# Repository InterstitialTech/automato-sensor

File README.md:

# automato-sensor
sensor module for the Automato ecosystem

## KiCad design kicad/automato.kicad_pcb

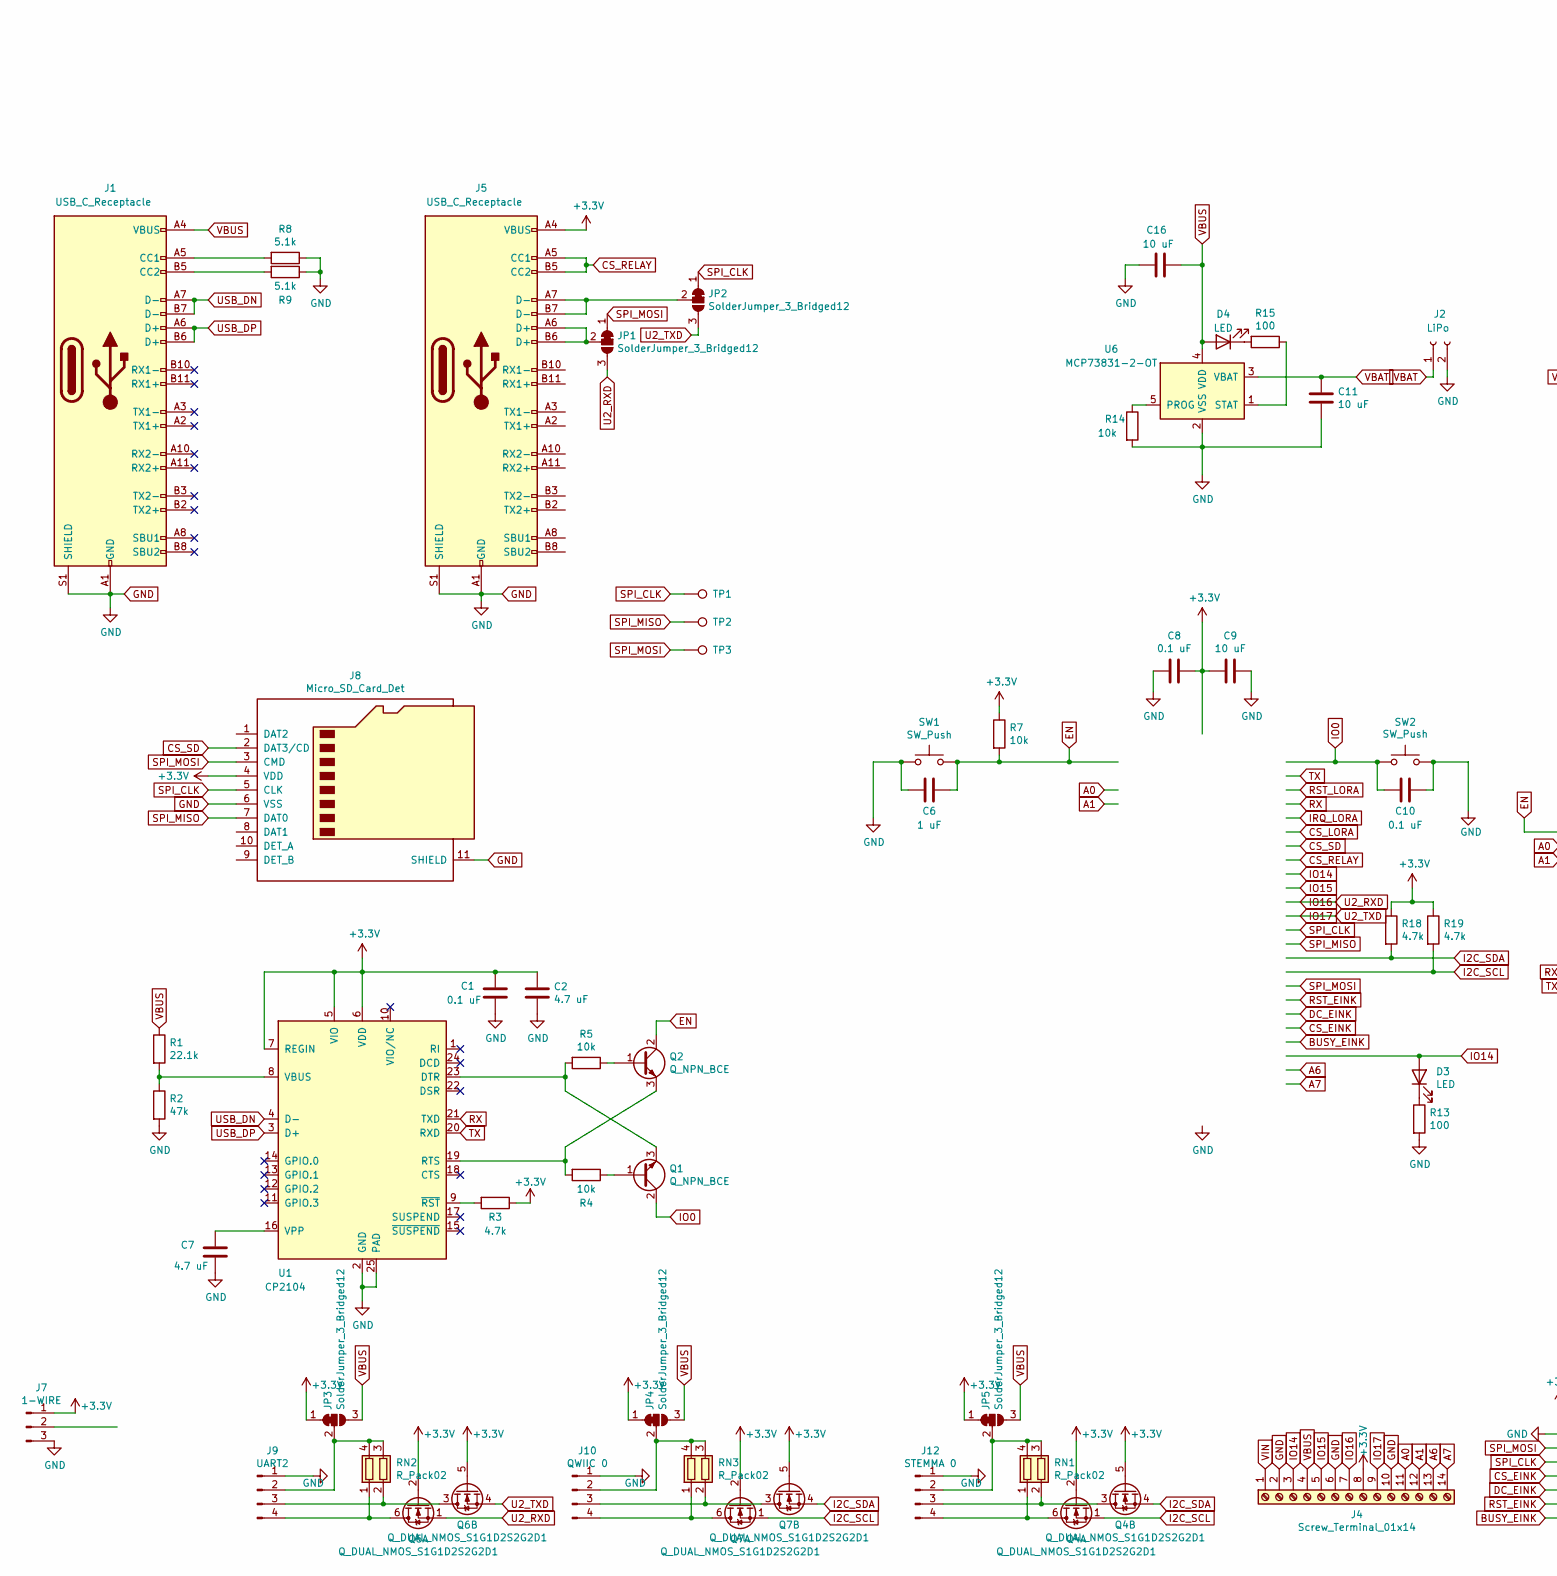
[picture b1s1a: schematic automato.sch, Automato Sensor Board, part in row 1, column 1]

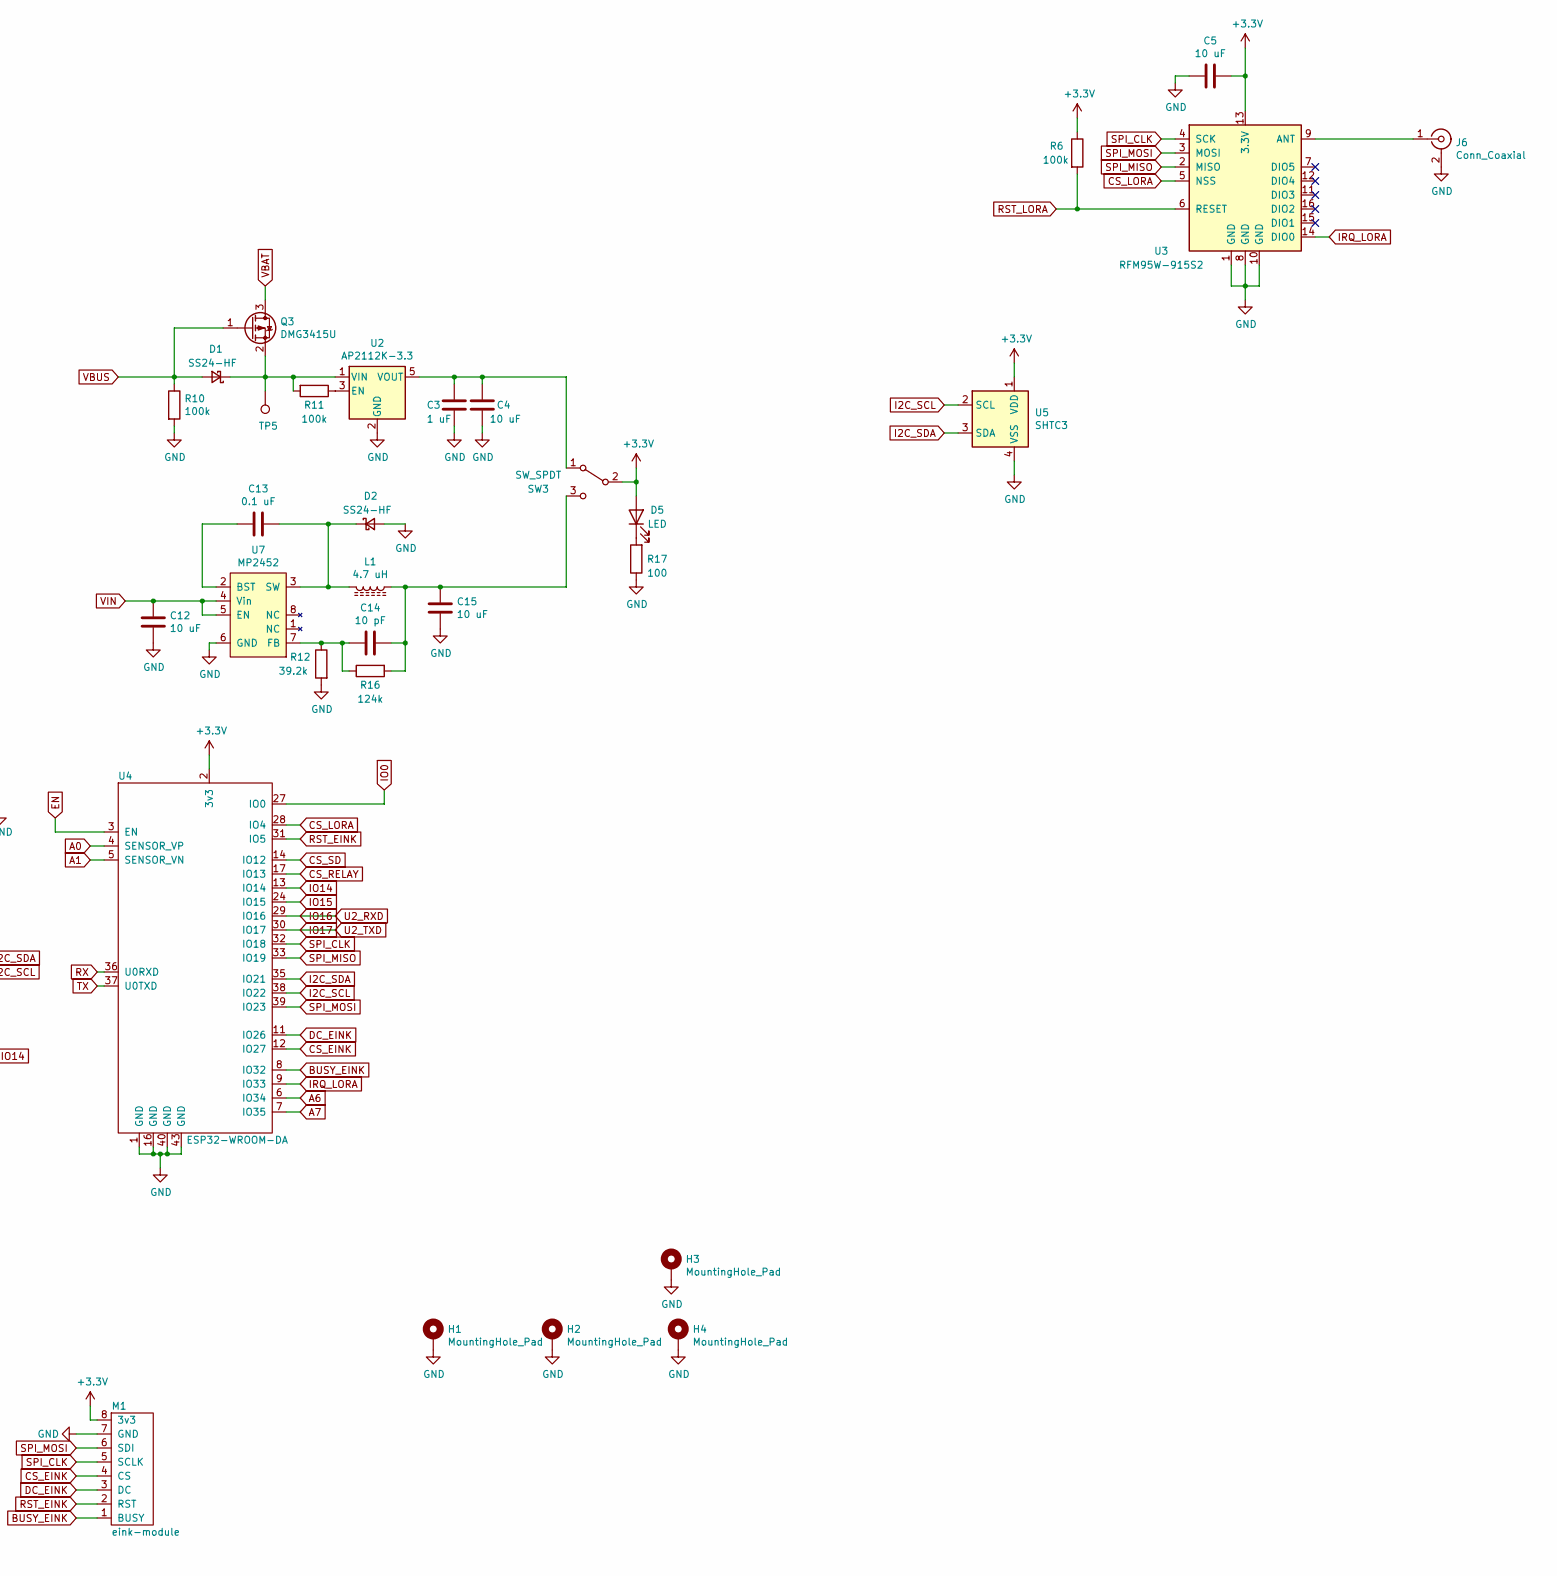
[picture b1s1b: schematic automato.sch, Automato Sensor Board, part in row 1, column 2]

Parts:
C1, C8, C10, C13: 0.1 uF; C_0805_2012Metric
C2, C7: 4.7 uF; C_0805_2012Metric
C3, C6: 1 uF; C_0805_2012Metric
C4, C5, C9, C11, C12, C15, C16: 10 uF; C_0805_2012Metric
C14: 10 pF; C_0805_2012Metric
D1, D2: SS24-HF; D_SMA
D3, D4, D5: LED; LED_0603_1608Metric_Castellated
H1, H2, H3, H4: MountingHole_Pad; MountingHole_3.2mm_M3_Pad_TopBottom
J1, J5: USB_C_Receptacle; USB_C_Receptacle_Amphenol_12401610E4-2A_CircularHoles
J2: LiPo; JST_PH_B2B-PH-K_1x02_P2.00mm_Vertical
J4: Screw_Terminal_01x14; TerminalBlock_Phoenix_PT-1,5-14-3.5-H_1x14_P3.50mm_Horizont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
J6: Conn_Coaxial; SMA_Molex_73251-1153_EdgeMount_Horizontal
J7: 1-WIRE; JST_PH_S3B-PH-SM4-TB_1x03-1MP_P2.00mm_Horizontal
J8: Micro_SD_Card_Det; MEM2051-00-195-00-A
J9: UART2; JST_PH_S4B-PH-SM4-TB_1x04-1MP_P2.00mm_Horizontal
J10: QWIIC 0; JST_SH_SM04B-SRSS-TB_1x04-1MP_P1.00mm_Horizontal
J12: STEMMA 0; JST_PH_S4B-PH-SM4-TB_1x04-1MP_P2.00mm_Horizontal
JP1, JP2, JP3, JP4, JP5: SolderJumper_3_Bridged12; SolderJumper-3_P1.3mm_Bridged12_RoundedPad1.0x1.5mm
L1: 4.7 uH; L_1008_2520Metric
M1: eink-module
Q1, Q2: Q_NPN_BCE; SOT-23
Q3: DMG3415U; SOT-23
Q4, Q6, Q7: Q_DUAL_NMOS_S1G1D2S2G2D1; SOT-23-6
R1: 22.1k; R_0805_2012Metric
R2: 47k; R_0805_2012Metric
R3, R18, R19: 4.7k; R_0805_2012Metric
R4, R5, R7, R14: 10k; R_0805_2012Metric
R6, R10, R11: 100k; R_0805_2012Metric
R8, R9: 5.1k; R_0805_2012Metric
R12: 39.2k; R_0805_2012Metric
R13, R15, R17: 100; R_0805_2012Metric
R16: 124k; R_0805_2012Metric
RN1, RN2, RN3: R_Pack02; R_Array_Concave_2x0603
SW1, SW2: SW_Push; SW_SPST_EVQPE1
SW3: SW_SPDT; L102021ML04Q
TP1, TP2, TP3, TP5: TestPoint; TestPoint_Pad_D2.0mm
U1: CP2104; QFN-24-1EP_4x4mm_P0.5mm_EP2.6x2.6mm
U2: AP2112K-3.3; SOT-23-5
U3: RFM95W-915S2; HOPERF_RFM9XW_SMD
U4: ESP32-WROOM-DA
U5: SHTC3; Sensirion_DFN-4-1EP_2x2mm_P1mm_EP0.7x1.6mm
U6: MCP73831-2-OT; SOT-23-5
U7: MP2452; DFN-8-1EP_3x2mm_P0.5mm_EP1.75x1.45mm

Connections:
+3V3: C1.1, C2.1, C5.1, C8.1, C9.2, D5.2 (A), J4.8, J5.A4 (VBUS), J5.A9 (VBUS), J5.B4 (VBUS), J5.B9 (VBUS), J7.1, J8.4 (VDD), JP3.1 (A), JP4.1 (A), JP5.1 (A), M1.8 (3v3), Q4.2 (G), Q4.5 (G), Q6.2 (G), Q6.5 (G), Q7.2 (G), Q7.5 (G), R3.1, R6.1, R7.1, R18.1, R19.1, SW3.2 (B), U1.5 (VIO), U1.6 (VDD), U1.7 (REGIN), U3.13 (3.3V), U4.2 (3v3), U5.1 (VDD)
A0: J4.11, U4.4 (SENSOR_VP)
A1: J4.12, U4.5 (SENSOR_VN)
A6: J4.13, U4.6 (IO34)
A7: J4.14, U4.7 (IO35)
BUSY_EINK: M1.1 (BUSY), U4.8 (IO32)
CS_EINK: M1.4 (CS), U4.12 (IO27)
CS_LORA: U3.5 (NSS), U4.28 (IO4)
CS_RELAY: J5.A5 (CC1), J5.B5 (CC2), U4.17 (IO13)
CS_SD: J8.2 (DAT3/CD), U4.14 (IO12)
DC_EINK: M1.3 (DC), U4.11 (IO26)
EN: C6.1, Q2.2 (C), R7.2, SW1.2, U4.3 (EN)
GND: C1.2, C2.2, C3.2, C4.2, C5.2, C6.2, C7.2, C8.2, C9.1, C10.1, C11.2, C12.2, C15.2, C16.1, D2.2 (A), H1.1, H2.1, H3.1, H4.1, J1.A1 (GND), J1.A12 (GND), J1.B1 (GND), J1.B12 (GND), J1.S1 (SHIELD), J2.2, J4.2, J4.6, J4.10, J5.A1 (GND), J5.A12 (GND), J5.B1 (GND), J5.B12 (GND), J5.S1 (SHIELD), J6.2 (Ext), J7.3, J8.6 (VSS), J8.11 (SHIELD), J9.1, J10.1, J12.1, M1.7 (GND), R2.2, R8.1, R9.1, R10.2, R12.2, R13.2, R14.2, R17.1, SW1.1, SW2.2, U1.2 (GND), U1.25 (PAD), U2.2 (GND), U3.1 (GND), U3.8 (GND), U3.10 (GND), U4.1 (GND), U4.16 (GND), U4.40 (GND), U4.43 (GND), U5.4 (VSS), U6.2 (VSS), U7.6 (GND)
I2C_SCL: Q4.1 (S), Q7.1 (S), R19.2, U4.38 (IO22), U5.2 (SCL)
I2C_SDA: Q4.4 (S), Q7.4 (S), R18.2, U4.35 (IO21), U5.3 (SDA)
IO0: C10.2, Q1.2 (C), SW2.1, U4.27 (IO0)
IO14: D3.2 (A), J4.3, U4.13 (IO14)
IO15: J4.5, U4.24 (IO15)
IO16: J4.7, JP1.3 (B), Q6.1 (S), U4.29 (IO16)
IO17: J4.9, JP2.3 (B), Q6.4 (S), U4.30 (IO17)
IRQ_LORA: U3.14 (DIO0), U4.9 (IO33)
unnamed: C3.1, C4.1, SW3.1 (A), U2.5 (VOUT)
unnamed: C7.1, U1.16 (VPP)
unnamed: C13.1, D2.1 (K), L1.2, U7.3 (SW)
unnamed: C13.2, U7.2 (BST)
unnamed: C14.1, R12.1, R16.1, U7.7 (FB)
unnamed: C14.2, C15.1, L1.1, R16.2, SW3.3 (C)
unnamed: D1.1 (K), Q3.2 (S), R11.2, TP5.1, U2.1 (VIN)
unnamed: D3.1 (K), R13.1
unnamed: D4.1 (K), R15.2
unnamed: D5.1 (K), R17.2
unnamed: J1.A5 (CC1), R8.2
unnamed: J1.B5 (CC2), R9.2
unnamed: J5.A6 (D+), J5.B6 (D+), JP1.2 (C)
unnamed: J5.A7 (D-), J5.B7 (D-), JP2.2 (C)
unnamed: J6.1 (In), U3.9 (ANT)
unnamed: J9.2, JP3.2 (C), RN2.3 (R2.2), RN2.4 (R1.2)
unnamed: J9.3, Q6.3 (D), RN2.2 (R2.1)
unnamed: J9.4, Q6.6 (D), RN2.1 (R1.1)
unnamed: J10.2, JP4.2 (C), RN3.3 (R2.2), RN3.4 (R1.2)
unnamed: J10.3, Q7.3 (D), RN3.2 (R2.1)
unnamed: J10.4, Q7.6 (D), RN3.1 (R1.1)
unnamed: J12.2, JP5.2 (C), RN1.3 (R2.2), RN1.4 (R1.2)
unnamed: J12.3, Q4.3 (D), RN1.2 (R2.1)
unnamed: J12.4, Q4.6 (D), RN1.1 (R1.1)
unnamed: Q1.1 (B), R4.1
unnamed: Q1.3 (E), R5.2, U1.23 (DTR)
unnamed: Q2.1 (B), R5.1
unnamed: Q2.3 (E), R4.2, U1.19 (RTS)
unnamed: R1.2, R2.1, U1.8 (VBUS)
unnamed: R3.2, U1.9 (~RST)
unnamed: R11.1, U2.3 (EN)
unnamed: R14.1, U6.5 (PROG)
unnamed: R15.1, U6.1 (STAT)
RST_EINK: M1.2 (RST), U4.31 (IO5)
RST_LORA: R6.2, U3.6 (RESET)
RX: U1.21 (TXD), U4.36 (U0RXD)
SPI_CLK: J8.5 (CLK), JP2.1 (A), M1.5 (SCLK), TP1.1, U3.4 (SCK), U4.32 (IO18)
SPI_MISO: J8.7 (DAT0), TP2.1, U3.2 (MISO), U4.33 (IO19)
SPI_MOSI: J8.3 (CMD), JP1.1 (A), M1.6 (SDI), TP3.1, U3.3 (MOSI), U4.39 (IO23)
TX: U1.20 (RXD), U4.37 (U0TXD)
USB_DN: J1.A7 (D-), J1.B7 (D-), U1.4 (D-)
USB_DP: J1.A6 (D+), J1.B6 (D+), U1.3 (D+)
VBAT: C11.1, J2.1, Q3.3 (D), U6.3 (VBAT)
VBUS: C16.2, D1.2 (A), D4.2 (A), J1.A4 (VBUS), J1.A9 (VBUS), J1.B4 (VBUS), J1.B9 (VBUS), J4.4, JP3.3 (B), JP4.3 (B), JP5.3 (B), Q3.1 (G), R1.1, R10.1, U6.4 (VDD)
VIN: C12.1, J4.1, U7.4 (Vin), U7.5 (EN)

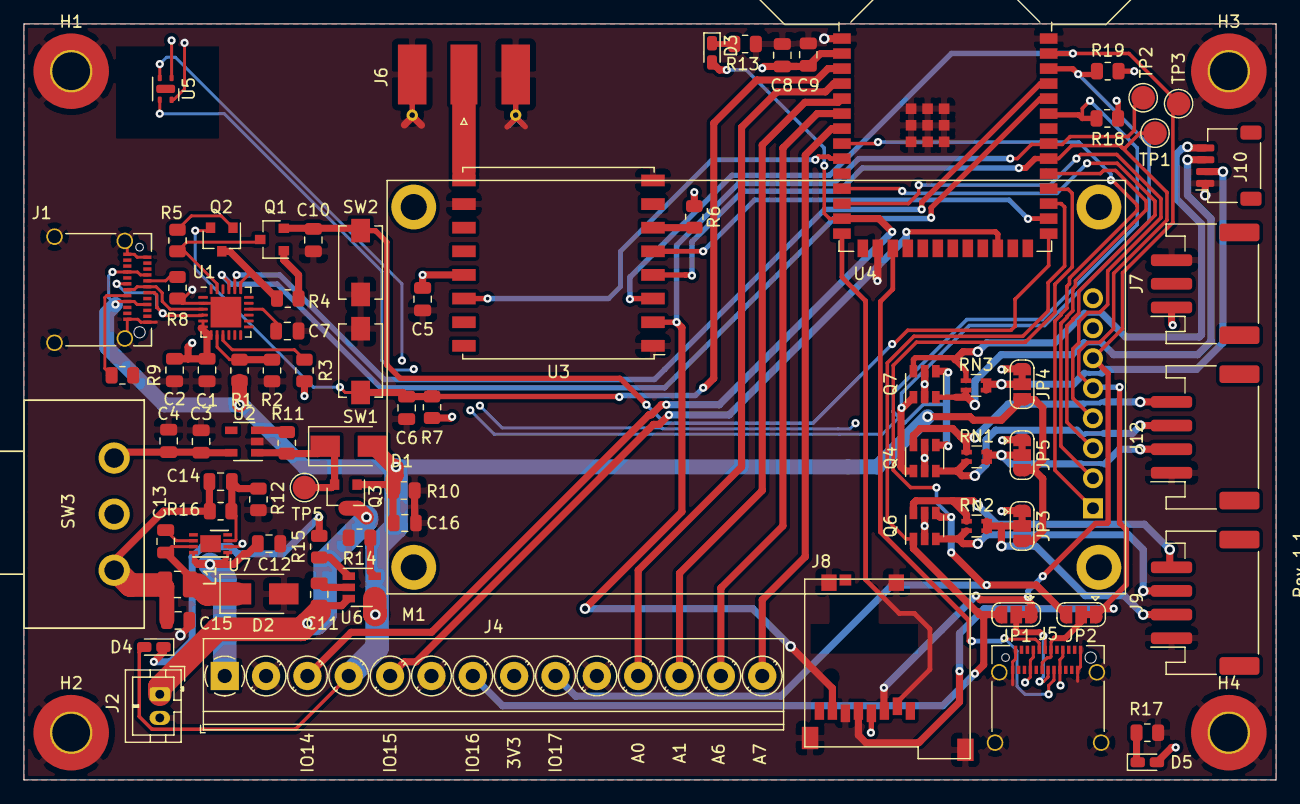
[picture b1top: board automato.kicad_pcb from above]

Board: 4 copper layers, 106.0 x 64.0 mm, 84 parts (0 on the bottom side), 66 nets.

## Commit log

2020-12-08 add power indicator LED
2020-12-08 add annotations
2020-12-08 add README.md
2020-12-08 add LICENSE
2020-12-11 correct regulator part no: AP2112K-3.3
2020-12-11 generate netlist
2020-12-19 add (most) footprints
2020-12-19 add bom.csv
2020-12-19 add SHC3 temp/humidity sensor
2020-12-20 add charge controller
2020-12-22 Added boost and buck regulators
    I still need to add some logic to enable/disable these regulators based on input voltage level/use case. I'm guessing the easiest thing for rev1 would be to have two separate inputs for the boost and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
2020-12-26 remove boost converter, connect buck via SPDT
2020-12-27 add analog pins: A0, A1, A6, A7
2020-12-28 add footprints: L1, Q3, SW3, LEDs, etc
2020-12-28 .gitignore: add .~lock.*
2020-12-28 add ILI9431_2.8in library symbol and footprint
2020-12-29 serialize designators, update Schottkys
2020-12-29 set all LED resistors to 100 ohms
2020-12-29 re-arrange schematic, update netlist
2020-12-29 J2: set footprint to JST_PH_B2B-PH-K_1x02_P2.00mm_Vertical
2020-12-29 fp-info-cache: resolve Sensor_Humidity footprint library
2020-12-29 Q3: fix pin numbering, update netlist
2020-12-31 lay out components (no tracks yet)
2020-12-31 layout: route traces
2021-01-01 fill GND and power planes, adjust traces
2021-01-03 layout: taper off right angles
2021-01-03 update LED footprints to 0603 castellated
2021-01-14 add layout and render images
2021-01-14 README.md: add images from assets
2021-01-15 consolidate C6 and C7
2021-01-15 ILI9341_2.8in: move outline from F.Mask to F.Silk
2021-01-15 layout: add mounting holes
2021-01-15 remove conflicting pads from USB-C receptacle
2021-01-15 add I2C pull-ups
2021-01-15 add test points
2021-01-15 add layour and render from 20210115
2021-01-15 README.md: update layout and render images
2021-01-26 switch to CP2104 (schematic and BOM)
2021-01-26 CP2104: update footprints and netlist
2021-01-26 correct DP/DN mixup
2021-01-26 CP2104: update layout
2021-01-28 layout: add back mounting holes
2021-01-31 add silkscreen contributions from John
2021-02-01 bom.csv: update U1 to CP2104
2021-02-05 reduce pad width on USB-C receptacle to 0.29 mm
2021-03-02 schematic: add metadata
2021-03-02 .gitignore: add kicad/_autosave-*
2021-03-02 add schematic, layout, and render from 20210131 (rev1)
2021-03-02 README: update assets to rev1 versions
2021-03-22 bom.csv: correct part number for C14
2021-03-22 revert to library-standard USB-C receptacle for J1
2021-03-22 increase hole diameter on SW3 to 1.65 mm
2021-10-06 rescue symbols (kicad 5.1.10)
2021-10-06 fix charge contoller support circuitry
    * R14: 5.1k -> 10k
    * C16: new 10 uF bypass capacitor for VBUS
    * update revision number to 1.1
    these changes intended to address the overheating problem
    with U6.
2022-06-07 add second usb c for serial
2022-07-01 ground new usb-c connection
2022-07-01 start 3-row servo-style headers
2022-07-01 add servo-style headers to pcb
2022-07-01 add footprints for headers
2022-07-01 a bit of reshuffling
2022-07-01 signal routing for relay-board spi
2022-07-10 add sd footprint, solder jumpers for optional usb-c uart
2022-07-10 add solder jumpers
    optional control of automato-relay with usb-c uart instead of usb-c spi.
2022-07-12 change 2x15 header symbol
2022-07-12 remove lcd
2022-07-13 remove servo style gpio headers
2022-07-13 update pcb
2022-07-13 moved battery charging circuit to clean up sch
2022-07-13 remove lcd, clean up some traces
2022-07-13 wiring for sd card, still need card detect
2022-07-21 add eink module
2022-07-21 add eink module to board
2022-07-21 updated pin assignments
2022-07-21 starting route
2022-07-21 rearrange power and usb-serial
2022-07-21 swapped io pin names on screw terminal
2022-07-21 improve sensor gpio screw terminal ordering
2022-07-21 flip vbus and 3v3
2022-07-24 add sma
2022-07-24 more routing
2022-07-24 reposition lora
2022-07-24 swapped cs_sd and cs_relay pins
2022-07-24 moved indicator led
2022-07-30 add qwiic, i2c, 1wire jst
2022-07-30 move some display pins around, change relay usb-c power to 3v3
2022-07-30 keep routing, add qwiic connectors, change layout to optimize for density and rf
2022-07-30 route gpoi's
2022-08-02 add stemma connectors
2022-08-05 adding more jst connectors, moving pin assignments
2022-08-05 add jst, re-route
2022-08-05 change tactile switch footprint
2022-08-17 add more standoffs to eink module
2022-08-17 finish JST route
2022-08-17 rip-up
2022-08-17 rearranging
2022-08-18 remove usb-c uart JST
2022-08-18 rearrange - component placement
2022-08-18 add i2c and uart level shifting
2022-08-18 temp-move lora to left side, add level shifting
2022-08-19 rearrange usb serial converter
2022-08-19 spaced out power supplies
2022-08-20 more route
2022-08-21 ADD esp32-wroom-da
2022-08-21 routing
2022-08-21 put mounting holes back
2022-08-25 writing in wroom-da
2022-08-25 playing with pins
2022-09-07 swapping to wroom-da
2022-09-07 swap in wroom-da, remove swd header
2022-09-07 finished routing
2022-09-08 update bom
2022-09-19 add mounting hole pads
2022-09-19 update wroom-da routing
2022-09-19 place mounting holes
2022-09-19 re-pour
2022-09-19 add sd card holder to library
2022-09-19 add new sd card
2022-09-19 finish bom
